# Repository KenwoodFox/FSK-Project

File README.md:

# FSK Analog Project

Done for EG330L at SNHU

# To Quickly Look At the design

Schematic [HERE](https://kicanvas.org/?repo=https://github.com/KenwoodFox/FSK-Project/blob/main/FSK%20Project.kicad_sch)  
PCB [HERE](https://kicanvas.org/?repo=https://github.com/KenwoodFox/FSK-Project/blob/main/FSK%20Project.kicad_pcb)

# To xmit the entire bee movie script
(the only valid benchmark ofc)

```shell
curl -s https://gist.githubusercontent.com/MattIPv4/045239bc27b16b2bcf7a3a9a4648c08a/raw/2411e31293a35f3e565f61e7490a806d4720ea7e/bee%2520movie%2520script | tee /dev/ttyUSB5
```

# Sending Serial/Testing

Configure Serial first

```shell
❯ minicom --device /dev/ttyUSB0 --baudrate 1200
```

Then you can cat+tee into the sender

```shell
❯ cat monk_syllabus.txt | tee /dev/ttyUSB0
```

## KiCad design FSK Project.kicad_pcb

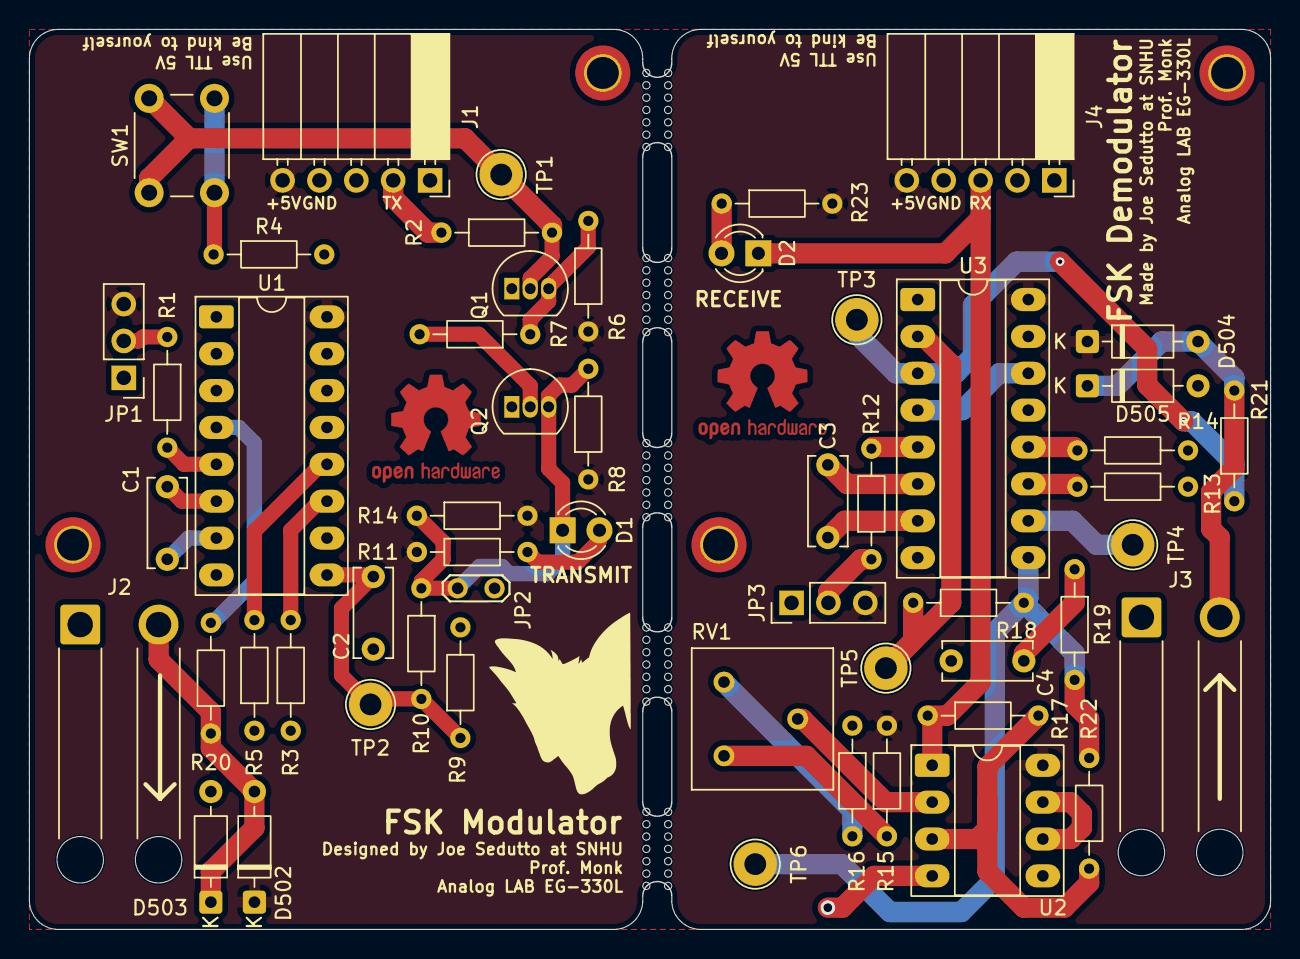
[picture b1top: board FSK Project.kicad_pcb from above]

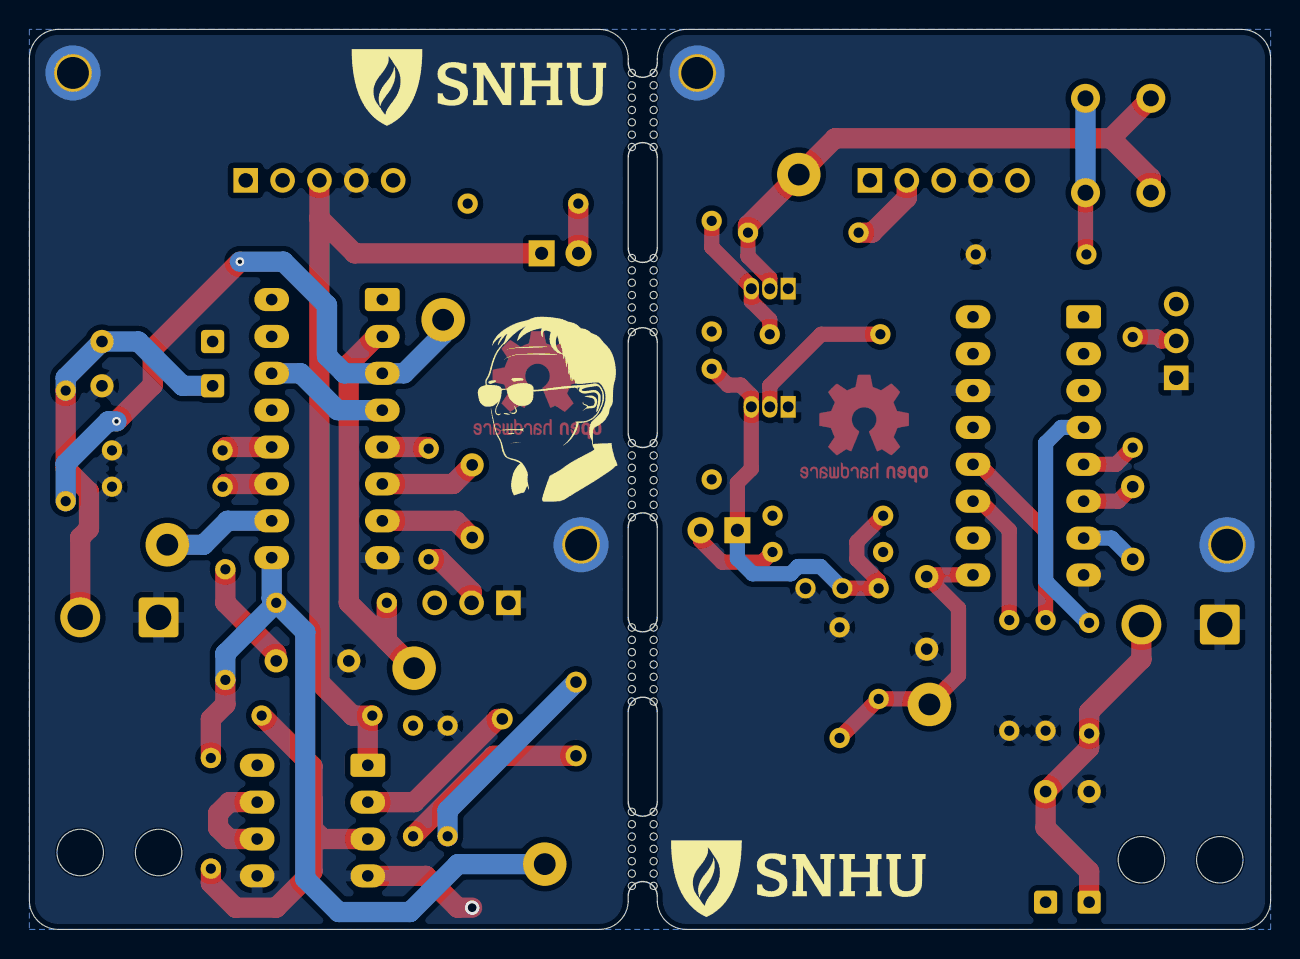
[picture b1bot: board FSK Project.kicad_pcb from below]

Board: 2 copper layers, 85.5 x 62.0 mm, 60 parts (2 on the bottom side), 38 nets.

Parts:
C1, C3, C4: 220pF; C_Disc_D6.0mm_W2.5mm_P5.00mm
C2: 47pF; C_Disc_D6.0mm_W2.5mm_P5.00mm
D1: TX; LED_D3.0mm
D2: RX; LED_D3.0mm
D502, D503, D504, D505: 1N4148; D_DO-35_SOD27_P7.62mm_Horizontal
H1, H2, H3, H4: MountingHole_Pad; MountingHole_2.2mm_M2_DIN965_Pad_TopBottom
J1: DATA IN; PinSocket_1x05_P2.54mm_Horizontal
J2: TX_PAIR; SolderWire-1sqmm_1x02_P5.4mm_D1.4mm_OD2.7mm_Relief
J3: RX_PAIR; SolderWire-1sqmm_1x02_P5.4mm_D1.4mm_OD2.7mm_Relief
J4: DATA_OUT; PinSocket_1x05_P2.54mm_Horizontal
JP1, JP3: INH; PinHeader_1x03_P2.54mm_Vertical
JP2: VCO; TestPoint_2Pads_Pitch2.54mm_Drill0.8mm
Q1, Q2: 2N3904; TO-92_Inline
R1, R9, R10, R12: 10K; R_Axial_DIN0204_L3.6mm_D1.6mm_P7.62mm_Horizontal
R2, R6, R7, R8: 1K; R_Axial_DIN0204_L3.6mm_D1.6mm_P7.62mm_Horizontal
R3, R13: 100k; R_Axial_DIN0204_L3.6mm_D1.6mm_P7.62mm_Horizontal
R4: 10R; R_Axial_DIN0204_L3.6mm_D1.6mm_P7.62mm_Horizontal
R5, R14#2: 47K; R_Axial_DIN0204_L3.6mm_D1.6mm_P7.62mm_Horizontal
R11, R23: 150R; R_Axial_DIN0204_L3.6mm_D1.6mm_P7.62mm_Horizontal
R14: 510K; R_Axial_DIN0204_L3.6mm_D1.6mm_P7.62mm_Horizontal
R15, R16, R22: 100K; R_Axial_DIN0204_L3.6mm_D1.6mm_P7.62mm_Horizontal
R17: 300K; R_Axial_DIN0204_L3.6mm_D1.6mm_P7.62mm_Horizontal
R18: 30K; R_Axial_DIN0204_L3.6mm_D1.6mm_P7.62mm_Horizontal
R19: 0R; R_Axial_DIN0204_L3.6mm_D1.6mm_P7.62mm_Horizontal
R20, R21: 100R; R_Axial_DIN0204_L3.6mm_D1.6mm_P7.62mm_Horizontal
RV1: 50K; Potentiometer_Bourns_3386F_Vertical
SNHU_NEW***: LOGO; SNHU_NEW
SNHU_NEW***#2: LOGO; SNHU_NEW
SW1: MAN; SW_PUSH_6mm
TP1, TP2: VCOin; TestPoint_Loop_D2.54mm_Drill1.5mm_Beaded
TP3: MOD_IN; TestPoint_Loop_D2.54mm_Drill1.5mm_Beaded
TP4: SFOUT; TestPoint_Loop_D2.54mm_Drill1.5mm_Beaded
TP5: PC2; TestPoint_Loop_D2.54mm_Drill1.5mm_Beaded
TP6: DEM_OUT; TestPoint_Loop_D2.54mm_Drill1.5mm_Beaded
U1, U3: MC14046BCP; DIP-16_W7.62mm_Socket_LongPads
U2: LM393; DIP-8_W7.62mm_Socket_LongPads

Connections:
+5V: D502.1 (K), D504.1 (K), J1.5, J4.5, JP1.3 (B), JP3.3 (B), R6.1, R8.1, R11.2, R14.2, R15.2, R23.2, U1.16 (VDD), U2.8 (V+), U3.16 (VDD)
/DATA_IN: D1.1 (K), JP2.1 (A), Q2.3 (C), R8.2, R10.1, R14.1
/DATA_OUT: D2.1 (K), J4.3, R17.1, U2.1
/DEM_OUT: R18.1, R19.2, R22.2, TP6.1 (1_1), U3.9 (VCOin)
/MOD_IN: R21.1, TP3.1 (1_1), U3.3 (RefIn)
/MOD_OUT: R20.2, U1.4 (FOUT)
GND: C2.2, C4.2, D503.2 (A), D505.2 (A), H1.1 (1_1), H2.1 (1_1), H3.1 (1_1), H4.1 (1_1), J1.4, J2.1, J3.1, J4.4, JP1.1 (A), JP2.2 (B), JP3.1 (A), Q1.1 (E), Q2.1 (E), R3.1, R4.2, R5.1, R9.2, R13.1, R14#2.1, R16.1, U1.8 (VSS), U1.14 (SigIn), U2.4 (V-), U2.5 (+), U3.8 (VSS)
unnamed: C4.1, R19.1
unnamed: D1.2 (A), R11.1
unnamed: D2.2 (A), R23.1
unnamed: D502.2 (A), D503.1 (K), J2.2, R20.1
unnamed: D504.2 (A), D505.1 (K), J3.2, R21.2
unnamed: J1.2, R2.1
unnamed: JP1.2 (C), R1.1
unnamed: JP3.2 (C), R12.1
unnamed: Q1.2 (B), R2.2, SW1.1, TP1.1 (1_1)
unnamed: Q1.3 (C), R6.2, R7.1
unnamed: Q2.2 (B), R7.2
unnamed: R4.1, SW1.2
unnamed: R15.1, RV1.1
unnamed: R16.2, RV1.3
unnamed: C1.1, U1.6 (C1)
unnamed: C1.2, U1.7 (C2)
unnamed: R1.2, U1.5 (Inh)
unnamed: R3.2, U1.11 (R1)
unnamed: R5.2, U1.12 (R2)
unnamed: C2.1, R9.1, R10.2, TP2.1 (1_1), U1.9 (VCOin)
unnamed: R17.2, R22.1, U2.3 (+)
unnamed: RV1.2, U2.2 (-)
unnamed: U2.6 (-), U2.7
unnamed: C3.1, U3.6 (C1)
unnamed: C3.2, U3.7 (C2)
unnamed: U3.4 (FOUT), U3.14 (SigIn)
unnamed: R12.2, U3.5 (Inh)
unnamed: R18.2, TP5.1 (1_1), U3.2 (PC1)
unnamed: R13.2, U3.11 (R1)
unnamed: R14#2.2, U3.12 (R2)
unnamed: TP4.1 (1_1), U3.10 (SFout)

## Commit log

2026-04-02 Inital
2026-04-02 Add page 5 filter information
2026-04-02 Add static protection
2026-04-02 Add outputs/gerbers for prod:
2026-04-02 Add final libs, include last leftover bits, fix op-amp and verify on board
2026-04-02 Export gerbers
2026-04-03 Add cool cutouts for ground probe grabs on back copper, not needed here but its neat
2026-04-05 Add writeup outline
2026-04-07 Get the writeup started
2026-04-07 Finish class for today
2026-04-18 fix some issues i made in the design oops
2026-04-23 Finish before class
